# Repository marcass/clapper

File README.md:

# clapper
Clapper switch for kids room

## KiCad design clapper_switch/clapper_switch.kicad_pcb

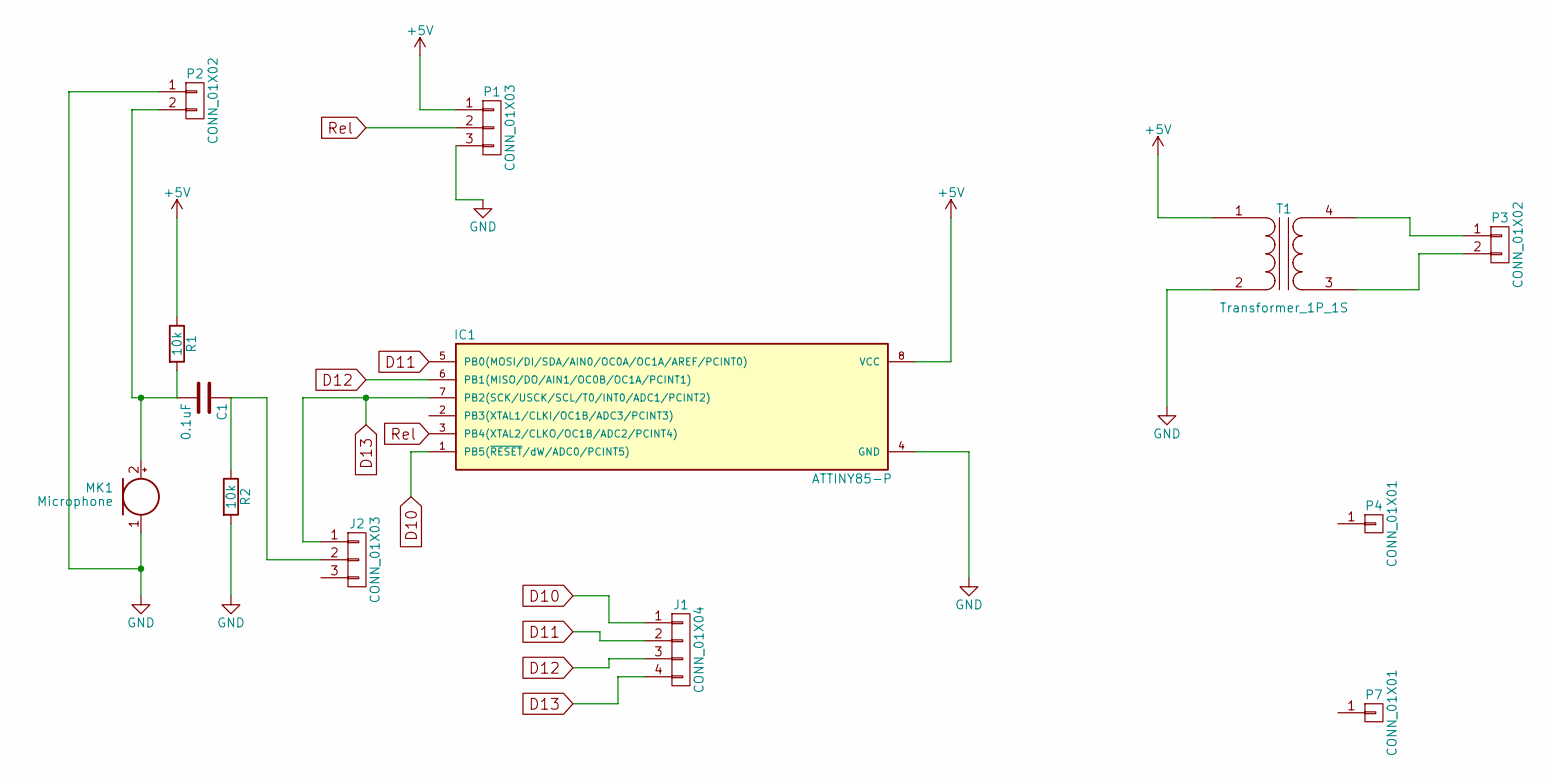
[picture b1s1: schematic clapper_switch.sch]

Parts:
C1: 0.1uF; C_Disc_D6_P5
IC1: ATTINY85-P; DIP-8_W7.62mm_LongPads
J1: CONN_01X04; Pin_Header_Straight_1x04_Pitch2.54mm
J2: CONN_01X03; Pin_Header_Straight_1x03_Pitch2.54mm
MK1: Microphone; TO-18_2Pin
P1: CONN_01X03; PhoenixContact_MCV-G_03x3.81mm_Vertical
P2, P3: CONN_01X02; PhoenixContact_MCV-G_02x3.81mm_Vertical
P4, P7: CONN_01X01; MountingHole_3.2mm_M3_DIN965_Pad
R1, R2: 10k; Resistor_SMD+THTuniversal_0805to1206_RM10_HandSoldering
T1: Transformer_1P_1S; TenstarRobot

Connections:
+5V: IC1.8 (VCC), P1.1, R1.1, T1.1 (AA)
D10: IC1.1 (PB5(~RESET~/dW/ADC0/PCINT5)), J1.1
D11: IC1.5 (PB0(MOSI/DI/SDA/AIN0/OC0A/OC1A/AREF/PCI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), J1.2
D12: IC1.6 (PB1(MISO/DO/AIN1/OC0B/OC1A/PCINT1)), J1.3
D13: IC1.7 (PB2(SCK/USCK/SCL/T0/INT0/ADC1/PCINT2)), J1.4, J2.1
GND: IC1.4 (GND), MK1.1 (-), P1.3, P2.1, R2.2, T1.2 (AB)
unnamed: C1.1, J2.2, R2.1
unnamed: C1.2, MK1.2 (+), P2.2, R1.2
unnamed: P3.1, T1.4 (SB)
unnamed: P3.2, T1.3 (SA)
Rel: IC1.3 (PB4(XTAL2/CLKO/OC1B/ADC2/PCINT4)), P1.2

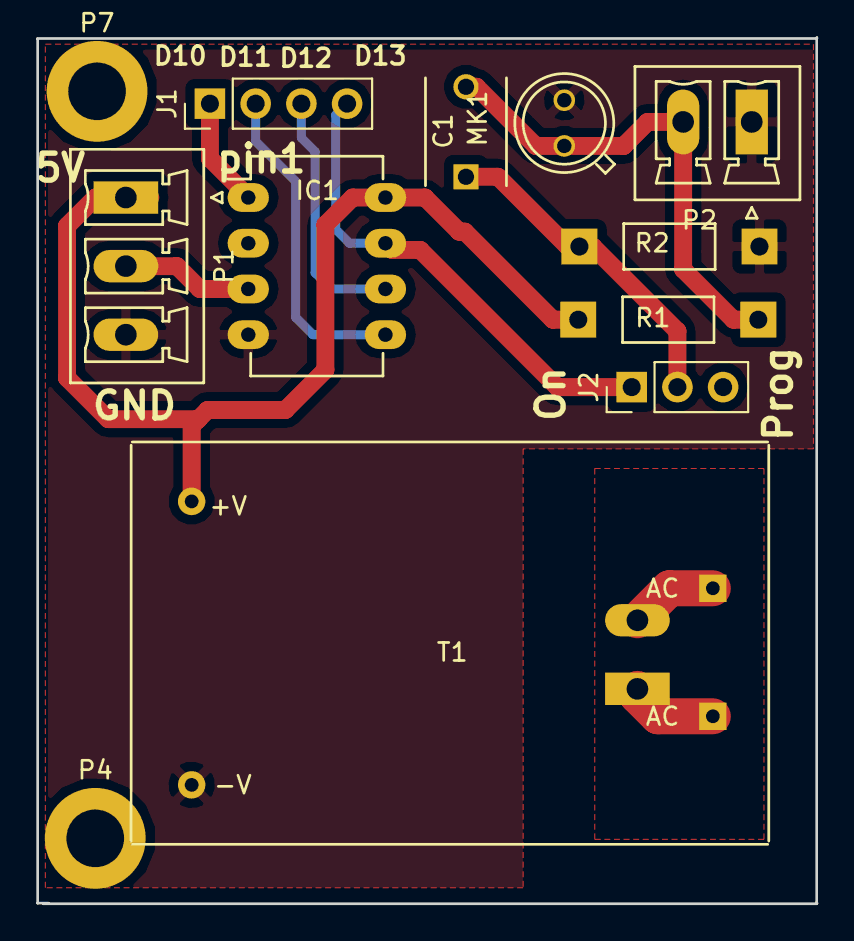
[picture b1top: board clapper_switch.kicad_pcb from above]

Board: 2 copper layers, 43.3 x 48.1 mm, 13 parts (1 on the bottom side), 11 nets.

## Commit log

2017-05-08 initial sketch
2017-05-09 refined code
2017-05-11 added start of PCB schematic
2017-07-17 finished layout
2017-07-29 final adjustments
2017-08-19 mods
